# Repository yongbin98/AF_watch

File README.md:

# BAMI_watch

This repository contains the C code used in the PPG/ECG Wearable Devices for Atrial Fibrillation Diagnosis System thesis study. 

The code is designed for a smartwatch equipped with the following components:
- PPG sensor: MAX86171
- ECG sensor: MAX30003
- IMU sensor: LSM6DS
- LCD display: ST7789
- Battery monitoring chip: MAX17262
- Bluetooth module: E104-BT5005A
- Other components: SD card, switch, speaker

The following protocols are used:
- SD card: Fatfs
- ARM::CMSIS: ver 5.8.0
- ARM::DSP: ver 1.9.0

The hardware architectures:

The Developed wearable watch :

The code was developed in the Keil IDE.

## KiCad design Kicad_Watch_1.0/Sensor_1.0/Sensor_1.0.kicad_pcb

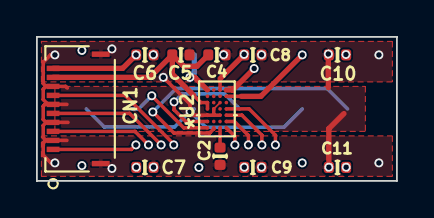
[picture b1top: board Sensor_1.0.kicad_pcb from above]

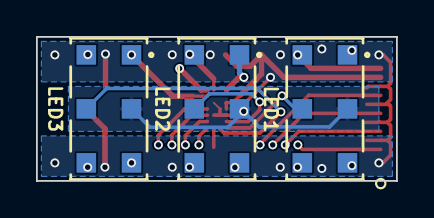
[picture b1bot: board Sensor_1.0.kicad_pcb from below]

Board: 4 copper layers, 20.0 x 8.0 mm, 14 parts (3 on the bottom side), 14 nets.

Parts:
C2: 1u; UL_C_0402_1005Metric
C4: 10u; UL_C_0402_1005Metric
C5: 0.1u; UL_C_0402_1005Metric
C6, C7, C8, C9, C10, C11: 22u; UL_C_0402_1005Metric
CN1: 503480-1000
LED1, LED2, LED3: SFH_7070; SFH7070
U2: MAX86171ENI+; MAX86171ENI&plus_

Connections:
+1V8: C4.1, C5.1, CN1.9, U2.D3 (VDD_ANA), U2.D4 (VDD_DIG)
/LED3_DRV: LED1.1, LED1.3, U2.A1 (LED3_DRV)
/LED4_DRV: LED2.1, LED2.3, U2.D1 (LED4_DRV)
/LED9_DRV: LED3.1, LED3.3, U2.A2 (LED9_DRV)
/PD1_IN: LED1.5, U2.D7 (PD1_IN)
/PD2_IN: LED2.5, U2.D6 (PD2_IN)
/PD3_IN: LED3.5, U2.C7 (PD3_IN)
/PPG_CS: CN1.7, U2.A7 (CSB/ADDR)
/PPG_MISO: CN1.3, U2.A5 (SDO)
/PPG_MOSI: CN1.5, U2.A6 (SDI/SDA)
/PPG_SCLK: CN1.1, U2.A4 (SCLK/SCL)
unnamed: C2.1, U2.B7 (VREF)
U_GND: C2.2, C4.2, C5.2, C6.2, C7.2, C8.2, C9.2, C10.2, C11.2, CN1.2, CN1.4, CN1.6, CN1.8, CN1.11, CN1.12, LED1.2, LED2.2, LED3.2, U2.B3 (PGND), U2.B5 (TRIG), U2.C4 (I2C_SEL), U2.C5 (GND), U2.D5 (PD_GND)
VDD: C6.1, C7.1, C8.1, C9.1, C10.1, C11.1, CN1.10, LED1.4, LED1.6, LED2.4, LED2.6, LED3.4, LED3.6, U2.B1 (VLED)

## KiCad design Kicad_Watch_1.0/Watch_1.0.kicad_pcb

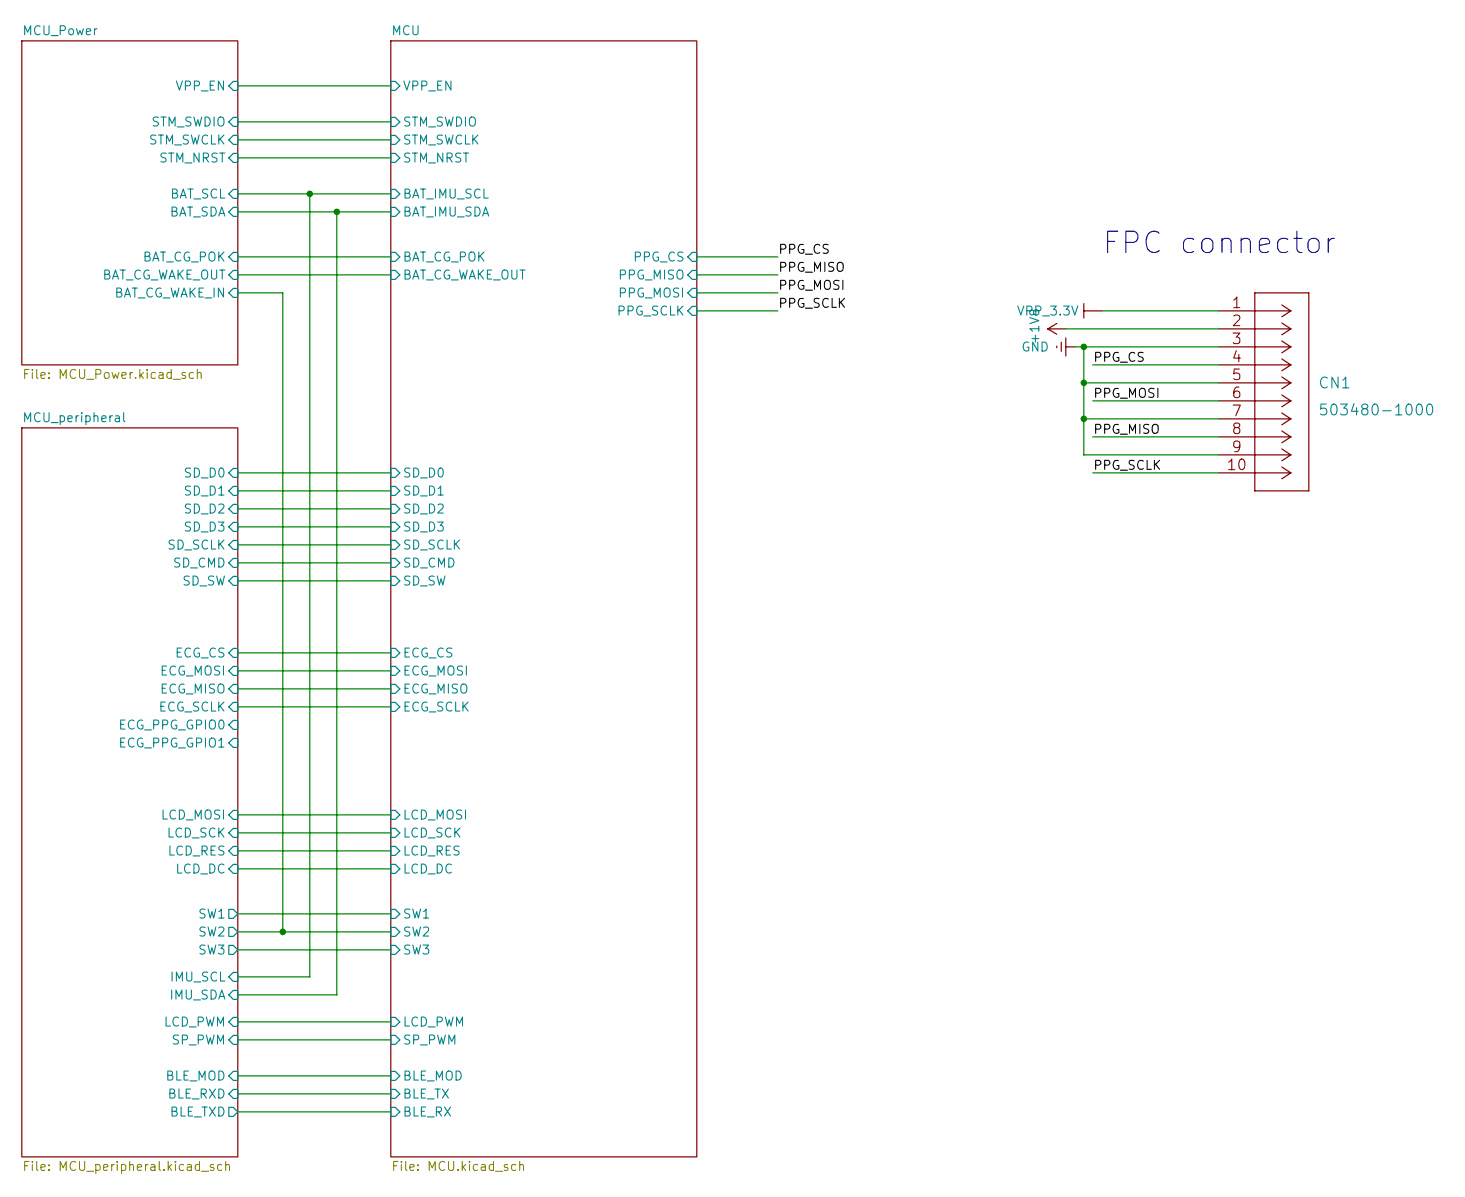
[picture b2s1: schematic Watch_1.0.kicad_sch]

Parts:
CN1: 503480-1000

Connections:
+1V8: CN1.2; also elsewhere on the board
/PPG_CS: CN1.4; also elsewhere on the board
/PPG_MISO: CN1.8; also elsewhere on the board
/PPG_MOSI: CN1.6; also elsewhere on the board
/PPG_SCLK: CN1.10; also elsewhere on the board
U_GND: CN1.3, CN1.5, CN1.7, CN1.9, CN1.11, CN1.12; also elsewhere on the board
VPP_3_3V: CN1.1; also elsewhere on the board

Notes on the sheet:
FPC connector

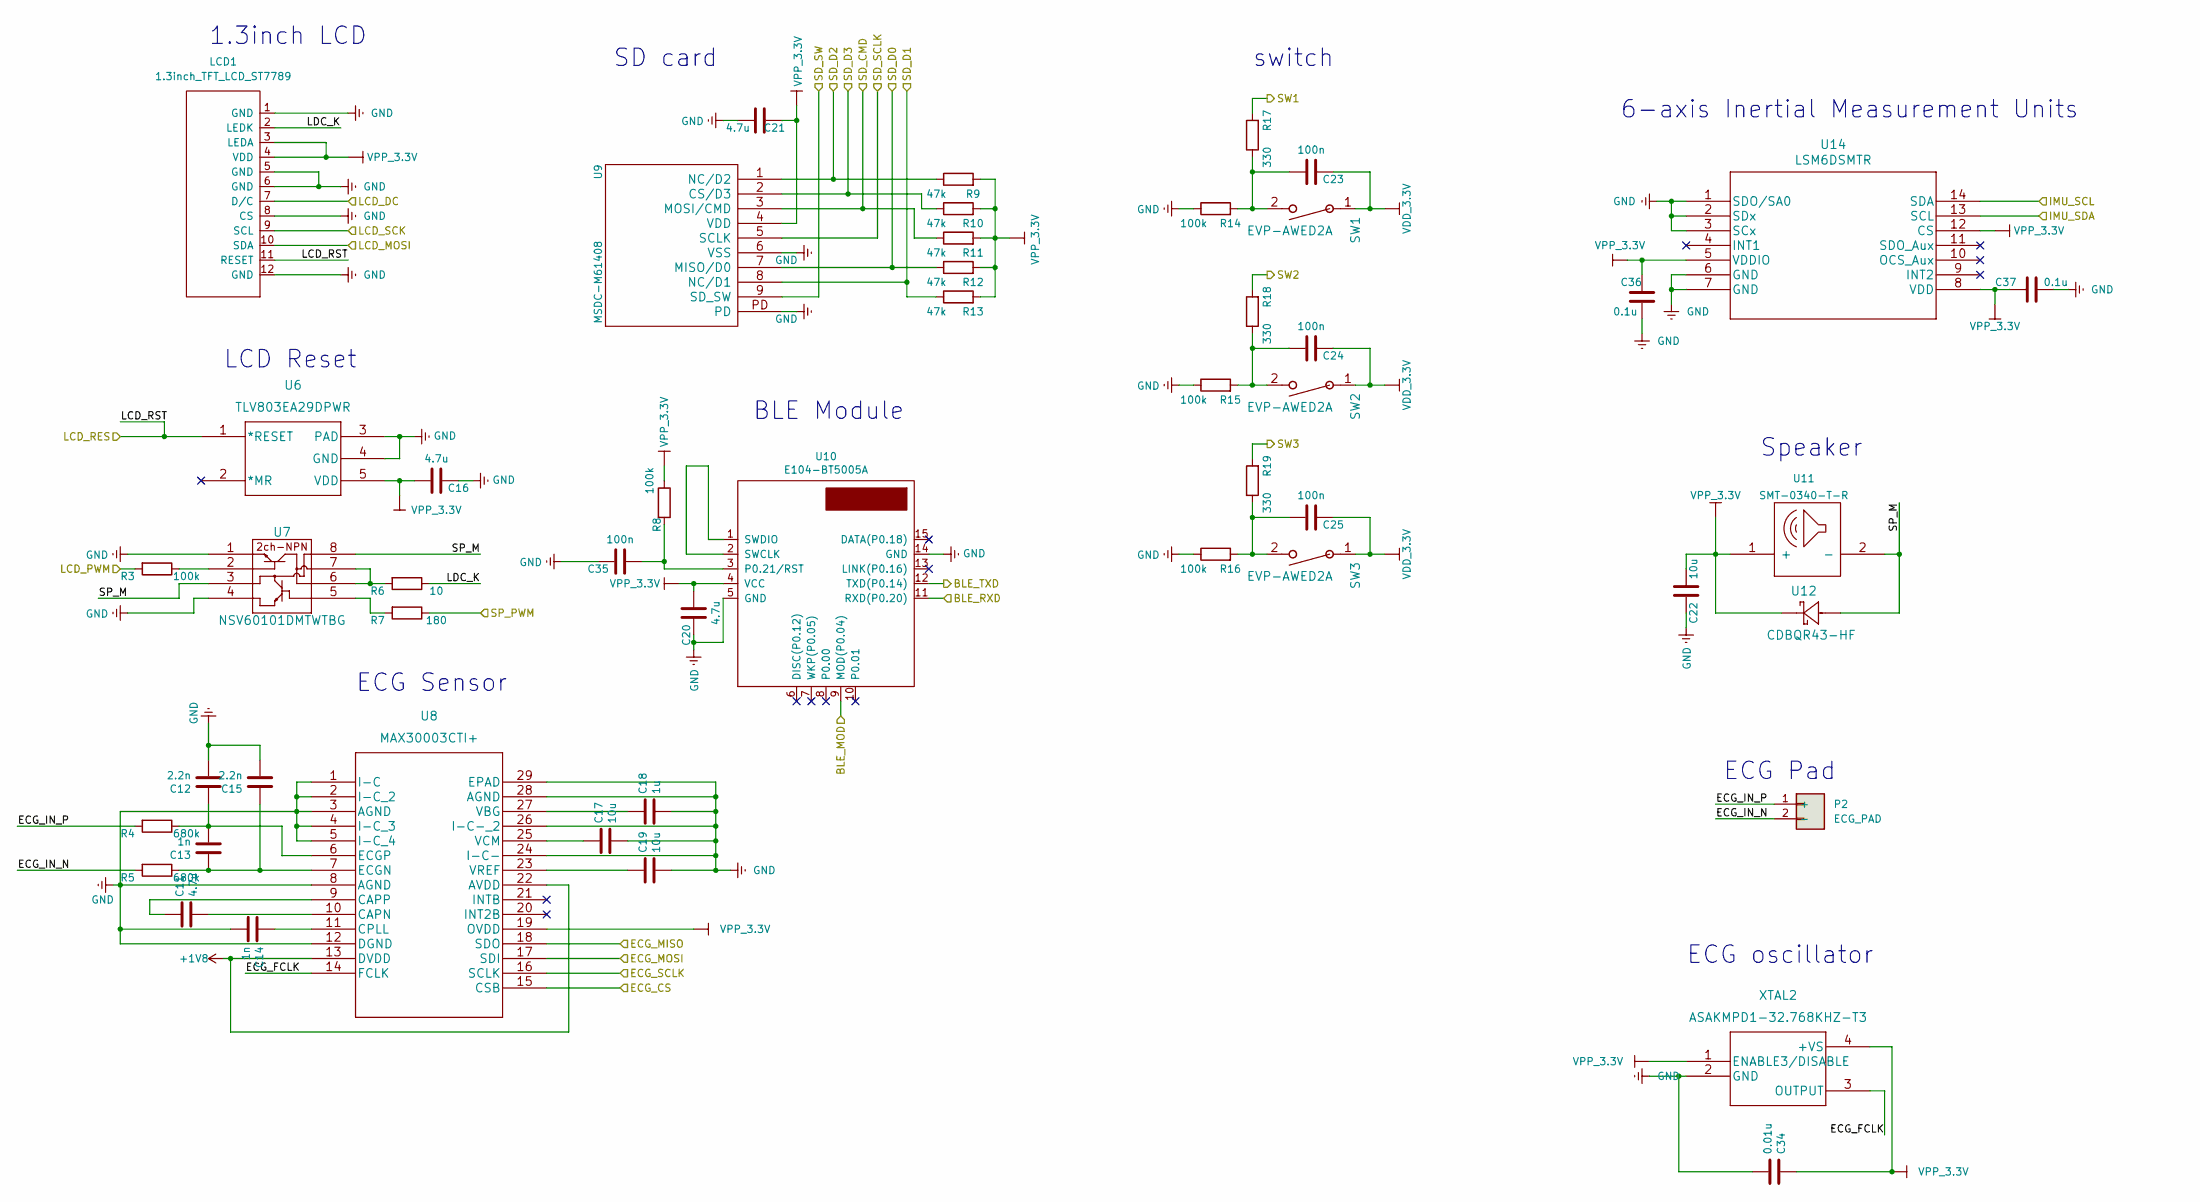
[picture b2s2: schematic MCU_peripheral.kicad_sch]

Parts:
C11, C16, C20, C21: 4.7u; UL_C_0402_1005Metric
C12, C15: 2.2n; UL_C_0402_1005Metric
C13, C14: 1n; UL_C_0402_1005Metric
C17, C19, C22: 10u; UL_C_0402_1005Metric
C18: 1u; UL_C_0402_1005Metric
C23, C24, C25, C35: 100n; UL_C_0402_1005Metric
C34: 0.01u; UL_C_0402_1005Metric
C36, C37: 0.1u; UL_C_0402_1005Metric
LCD1: 1.3inch_TFT_LCD_ST7789
P2: ECG_PAD
R3, R8, R14, R15, R16: 100k; R_0402_1005Metric
R4, R5: 680k; R_0402_1005Metric
R6: 10; R_0402_1005Metric
R7: 180; R_0402_1005Metric
R9, R10, R11, R12, R13: 47k; R_0402_1005Metric
R17, R18, R19: 330; R_0402_1005Metric
SW1, SW2, SW3: EVP-AWED2A
U6: TLV803EA29DPWR
U7: NSV60101DMTWTBG
U8: MAX30003CTI+; MAX30003CTI&plus_
U9: MSDC-M61408; MSDC-M61408(Micro_SD)
U10: E104-BT5005A; E104-BT5005A_QFN-15_9x9_Pitch1.1mm
U11: SMT-0340-T-R
U12: CDBQR43-HF
U14: LSM6DSMTR
XTAL2: ASAKMPD1-32.768KHZ-T3

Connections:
+1V8: U8.13 (DVDD), U8.22 (AVDD); also elsewhere on the board
/MCU/BAT_IMU_SCL: U14.14 (SDA); also elsewhere on the board
/MCU/BAT_IMU_SDA: U14.13 (SCL); also elsewhere on the board
/MCU/BLE_MOD: U10.9 (MOD(P0.04)); also elsewhere on the board
/MCU/BLE_RX: U10.12 (TXD(P0.14)); also elsewhere on the board
/MCU/BLE_TX: U10.11 (RXD(P0.20)); also elsewhere on the board
/MCU/ECG_CS: U8.15 (CSB); also elsewhere on the board
/MCU/ECG_MISO: U8.18 (SDO); also elsewhere on the board
/MCU/ECG_MOSI: U8.17 (SDI); also elsewhere on the board
/MCU/ECG_SCLK: U8.16 (SCLK); also elsewhere on the board
/MCU/LCD_DC: LCD1.7 (D/C); also elsewhere on the board
/MCU/LCD_MOSI: LCD1.10 (SDA); also elsewhere on the board
/MCU/LCD_PWM: R3.2; also elsewhere on the board
/MCU/LCD_SCK: LCD1.9 (SCL); also elsewhere on the board
/MCU/SD_CMD: R11.1, U9.3 (MOSI/CMD); also elsewhere on the board
/MCU/SD_D0: R12.1, U9.7 (MISO/D0); also elsewhere on the board
/MCU/SD_D1: R13.1, U9.8 (NC/D1); also elsewhere on the board
/MCU/SD_D2: R9.1, U9.1 (NC/D2); also elsewhere on the board
/MCU/SD_D3: R10.1, U9.2 (CS/D3); also elsewhere on the board
/MCU/SD_SCLK: U9.5 (SCLK); also elsewhere on the board
/MCU/SD_SW: U9.9 (SD_SW); also elsewhere on the board
/MCU/SP_PWM: R7.1; also elsewhere on the board
/MCU/SW1: R17.2; also elsewhere on the board
/MCU/SW2: R18.2; also elsewhere on the board
/MCU/SW3: R19.2; also elsewhere on the board
/MCU_peripheral/ECG_FCLK: U8.14 (FCLK), XTAL2.3 (OUTPUT)
/MCU_peripheral/ECG_IN_N: P2.2 (-), R5.2
/MCU_peripheral/ECG_IN_P: P2.1 (+), R4.2
/MCU_peripheral/LCD_RST: LCD1.11 (RESET), U6.1 (*RESET); also elsewhere on the board
/MCU_peripheral/LDC_K: LCD1.2 (LEDK), R6.1
/MCU_peripheral/SP_M: U7.3, U7.8, U11.2 (-), U12.2
unnamed: C11.1, U8.9 (CAPP)
unnamed: C11.2, U8.10 (CAPN)
unnamed: C12.1, C13.2, R4.1, U8.6 (ECGP)
unnamed: C13.1, C15.1, R5.1, U8.7 (ECGN)
unnamed: C14.1, U8.11 (CPLL)
unnamed: C17.1, U8.25 (VCM)
unnamed: C18.1, U8.27 (VBG)
unnamed: C19.1, U8.23 (VREF)
unnamed: C23.2, R14.2, R17.1, SW1.2
unnamed: C24.2, R15.2, R18.1, SW2.2
unnamed: C25.2, R16.2, R19.1, SW3.2
unnamed: C35.2, R8.2, U10.3 (P0.21/RST)
unnamed: R3.1, U7.2
unnamed: R6.2, U7.6, U7.7
unnamed: R7.2, U7.5
unnamed: U10.1 (SWDIO), U10.2 (SWCLK)
U_GND: C12.2, C14.2, C15.2, C16.1, C17.2, C18.2, C19.2, C20.1, C21.1, C22.1, C34.2, C35.1, C36.2, C37.2, LCD1.1 (GND), LCD1.5 (GND), LCD1.6 (GND), LCD1.8 (CS), LCD1.12 (GND), R14.1, R15.1, R16.1, U6.3 (PAD), U6.4 (GND), U7.1, U7.4, U8.1 (I-C), U8.2 (I-C_2), U8.3 (AGND), U8.4 (I-C_3), U8.5 (I-C_4), U8.8 (AGND), U8.12 (DGND), U8.24 (I-C-), U8.26 (I-C-_2), U8.28 (AGND), U8.29 (EPAD), U9.6 (VSS), U9.PD, U10.5 (GND), U10.14 (GND), U14.1 (SDO/SA0), U14.2 (SDx), U14.3 (SCx), U14.6 (GND), U14.7 (GND), XTAL2.2 (GND); also elsewhere on the board
VDD_3_3V: C23.1, C24.1, C25.1, SW1.1, SW2.1, SW3.1; also elsewhere on the board
VPP_3_3V: C16.2, C20.2, C21.2, C22.2, C34.1, C36.1, C37.1, LCD1.3 (LEDA), LCD1.4 (VDD), R8.1, R9.2, R10.2, R11.2, R12.2, R13.2, U6.5 (VDD), U8.19 (OVDD), U9.4 (VDD), U10.4 (VCC), U11.1 (+), U12.1, U14.5 (VDDIO), U14.8 (VDD), U14.12 (CS), XTAL2.1 (ENABLE3/DISABLE), XTAL2.4 (+VS); also elsewhere on the board

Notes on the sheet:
6-axis Inertial Measurement Units
Speaker
switch
ECG Pad
1.3inch LCD
LCD Reset
BLE Module
SD card
ECG oscillator
ECG Sensor

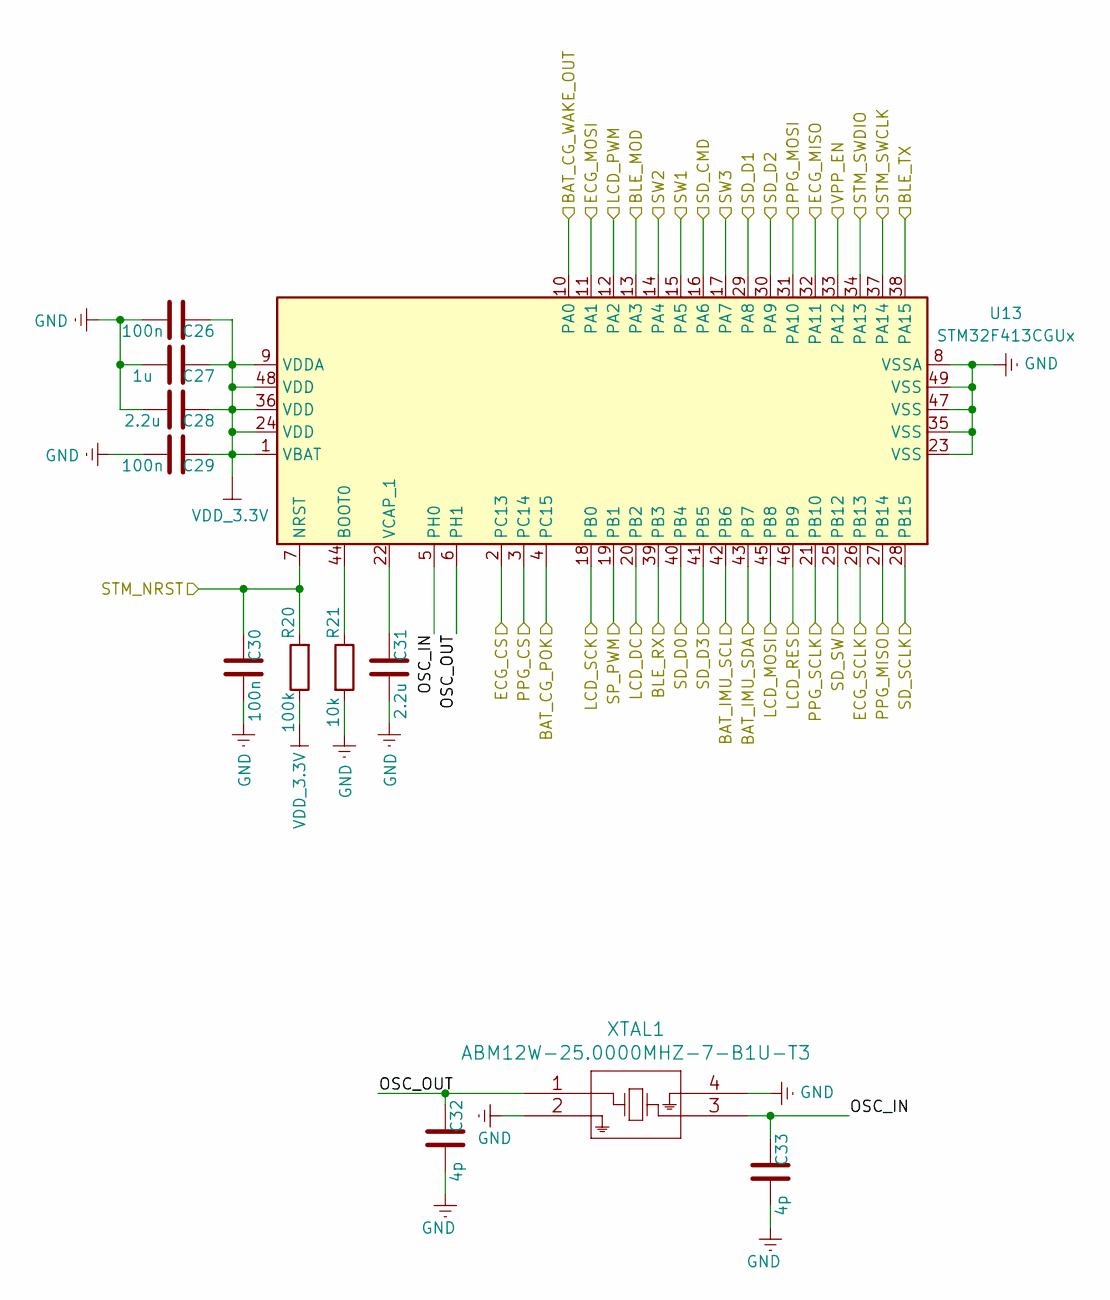
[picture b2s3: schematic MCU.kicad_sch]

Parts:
C26, C29, C30: 100n; UL_C_0402_1005Metric
C27: 1u; UL_C_0402_1005Metric
C28, C31: 2.2u; UL_C_0402_1005Metric
C32, C33: 4p; UL_C_0402_1005Metric
R20: 100k; R_0402_1005Metric
R21: 10k; R_0402_1005Metric
U13: STM32F413CGUx; QFN-48-1EP_7x7mm_P0.5mm_EP5.6x5.6mm
XTAL1: ABM12W-25.0000MHZ-7-B1U-T3; ABM12W

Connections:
/MCU/BAT_CG_POK: U13.4 (PC15); also elsewhere on the board
/MCU/BAT_CG_WAKE_OUT: U13.10 (PA0); also elsewhere on the board
/MCU/BAT_IMU_SCL: U13.42 (PB6); also elsewhere on the board
/MCU/BAT_IMU_SDA: U13.43 (PB7); also elsewhere on the board
/MCU/BLE_MOD: U13.13 (PA3); also elsewhere on the board
/MCU/BLE_RX: U13.39 (PB3); also elsewhere on the board
/MCU/BLE_TX: U13.38 (PA15); also elsewhere on the board
/MCU/ECG_CS: U13.2 (PC13); also elsewhere on the board
/MCU/ECG_MISO: U13.32 (PA11); also elsewhere on the board
/MCU/ECG_MOSI: U13.11 (PA1); also elsewhere on the board
/MCU/ECG_SCLK: U13.26 (PB13); also elsewhere on the board
/MCU/LCD_DC: U13.20 (PB2); also elsewhere on the board
/MCU/LCD_MOSI: U13.45 (PB8); also elsewhere on the board
/MCU/LCD_PWM: U13.12 (PA2); also elsewhere on the board
/MCU/LCD_SCK: U13.18 (PB0); also elsewhere on the board
/MCU/OSC_IN: C33.2, U13.5 (PH0), XTAL1.3
/MCU/OSC_OUT: C32.2, U13.6 (PH1), XTAL1.1
/MCU/SD_CMD: U13.16 (PA6); also elsewhere on the board
/MCU/SD_D0: U13.40 (PB4); also elsewhere on the board
/MCU/SD_D1: U13.29 (PA8); also elsewhere on the board
/MCU/SD_D2: U13.30 (PA9); also elsewhere on the board
/MCU/SD_D3: U13.41 (PB5); also elsewhere on the board
/MCU/SD_SCLK: U13.28 (PB15); also elsewhere on the board
/MCU/SD_SW: U13.25 (PB12); also elsewhere on the board
/MCU/SP_PWM: U13.19 (PB1); also elsewhere on the board
/MCU/STM_NRST: C30.2, R20.2, U13.7 (NRST); also elsewhere on the board
/MCU/STM_SWCLK: U13.37 (PA14); also elsewhere on the board
/MCU/STM_SWDIO: U13.34 (PA13); also elsewhere on the board
/MCU/SW1: U13.15 (PA5); also elsewhere on the board
/MCU/SW2: U13.14 (PA4); also elsewhere on the board
/MCU/SW3: U13.17 (PA7); also elsewhere on the board
/MCU/VPP_EN: U13.33 (PA12); also elsewhere on the board
/MCU_peripheral/LCD_RST: U13.46 (PB9); also elsewhere on the board
/PPG_CS: U13.3 (PC14); also elsewhere on the board
/PPG_MISO: U13.27 (PB14); also elsewhere on the board
/PPG_MOSI: U13.31 (PA10); also elsewhere on the board
/PPG_SCLK: U13.21 (PB10); also elsewhere on the board
unnamed: C31.2, U13.22 (VCAP_1)
unnamed: R21.1, U13.44 (BOOT0)
U_GND: C26.1, C27.1, C28.1, C29.1, C30.1, C31.1, C32.1, C33.1, R21.2, U13.8 (VSSA), U13.23 (VSS), U13.35 (VSS), U13.47 (VSS), U13.49 (VSS), XTAL1.2, XTAL1.4; also elsewhere on the board
VDD_3_3V: C26.2, C27.2, C28.2, C29.2, R20.1, U13.1 (VBAT), U13.9 (VDDA), U13.24 (VDD), U13.36 (VDD), U13.48 (VDD); also elsewhere on the board

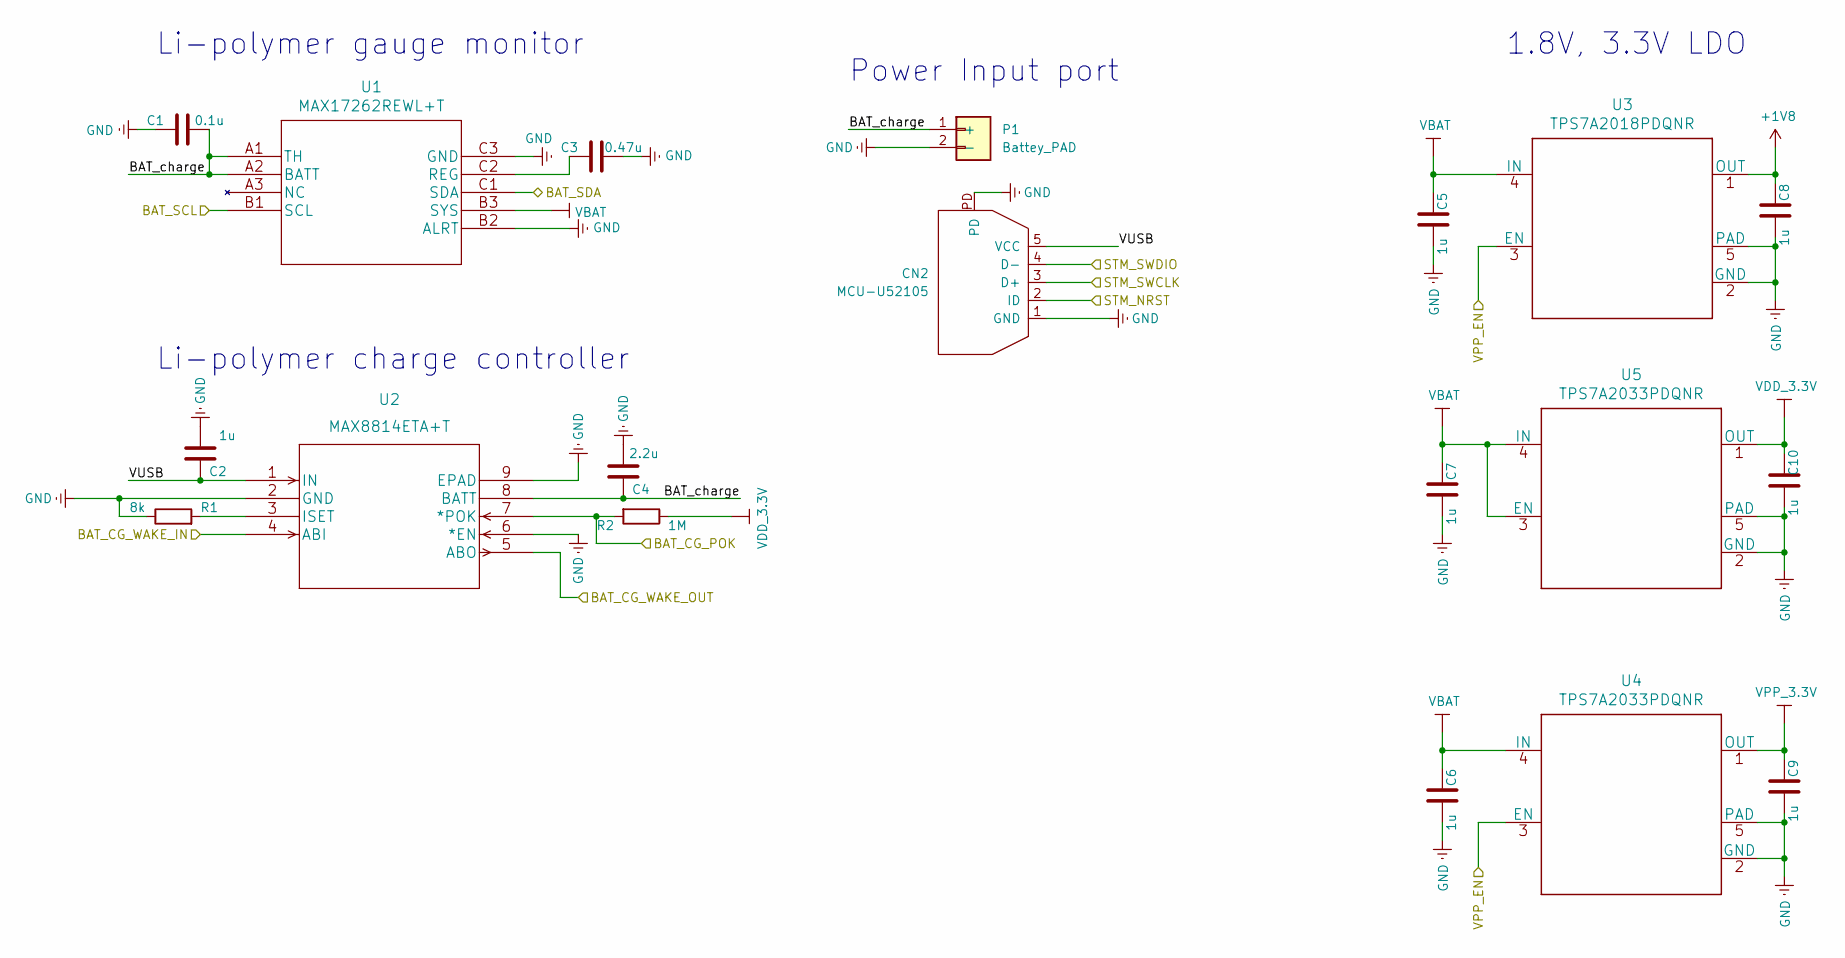
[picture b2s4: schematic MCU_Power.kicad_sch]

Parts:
C1: 0.1u; UL_C_0402_1005Metric
C2, C5, C6, C7, C8, C9, C10: 1u; UL_C_0402_1005Metric
C3: 0.47u; UL_C_0402_1005Metric
C4: 2.2u; UL_C_0402_1005Metric
CN2: MCU-U52105
P1: Battey_PAD
R1: 8k; R_0402_1005Metric
R2: 1M; R_0402_1005Metric
U1: MAX17262REWL+T; MAX17262REWL&plus_T
U2: MAX8814ETA+T; MAX8814ETA&plus_T
U3: TPS7A2018PDQNR; X2SON-4PIN
U4, U5: TPS7A2033PDQNR; X2SON-4PIN

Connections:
+1V8: C8.2, U3.1 (OUT); also elsewhere on the board
/MCU/BAT_CG_POK: R2.2, U2.7 (*POK); also elsewhere on the board
/MCU/BAT_CG_WAKE_OUT: U2.5 (ABO); also elsewhere on the board
/MCU/BAT_IMU_SCL: U1.B1 (SCL); also elsewhere on the board
/MCU/BAT_IMU_SDA: U1.C1 (SDA); also elsewhere on the board
/MCU/STM_NRST: CN2.2 (ID); also elsewhere on the board
/MCU/STM_SWCLK: CN2.3 (D+); also elsewhere on the board
/MCU/STM_SWDIO: CN2.4 (D-); also elsewhere on the board
/MCU/SW2: U2.4 (ABI); also elsewhere on the board
/MCU/VPP_EN: U3.3 (EN), U4.3 (EN); also elsewhere on the board
/MCU_Power/BAT_charge: C1.2, C4.1, P1.1 (+), U1.A1 (TH), U1.A2 (BATT), U2.8 (BATT)
/MCU_Power/VUSB: C2.1, CN2.5 (VCC), U2.1 (IN)
unnamed: C3.2, U1.C2 (REG)
unnamed: R1.2, U2.3 (ISET)
U_GND: C1.1, C2.2, C3.1, C4.2, C5.1, C6.1, C7.1, C8.1, C9.1, C10.1, CN2.1 (GND), CN2.PD, P1.2 (-), R1.1, U1.B2 (ALRT), U1.C3 (GND), U2.2 (GND), U2.6 (*EN), U2.9 (EPAD), U3.2 (GND), U3.5 (PAD), U4.2 (GND), U4.5 (PAD), U5.2 (GND), U5.5 (PAD); also elsewhere on the board
VBAT: C5.2, C6.2, C7.2, U1.B3 (SYS), U3.4 (IN), U4.4 (IN), U5.3 (EN), U5.4 (IN)
VDD_3_3V: C10.2, R2.1, U5.1 (OUT); also elsewhere on the board
VPP_3_3V: C9.2, U4.1 (OUT); also elsewhere on the board

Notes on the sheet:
Li-polymer charge controller
Li-polymer gauge monitor
1.8V, 3.3V LDO
Power Input port

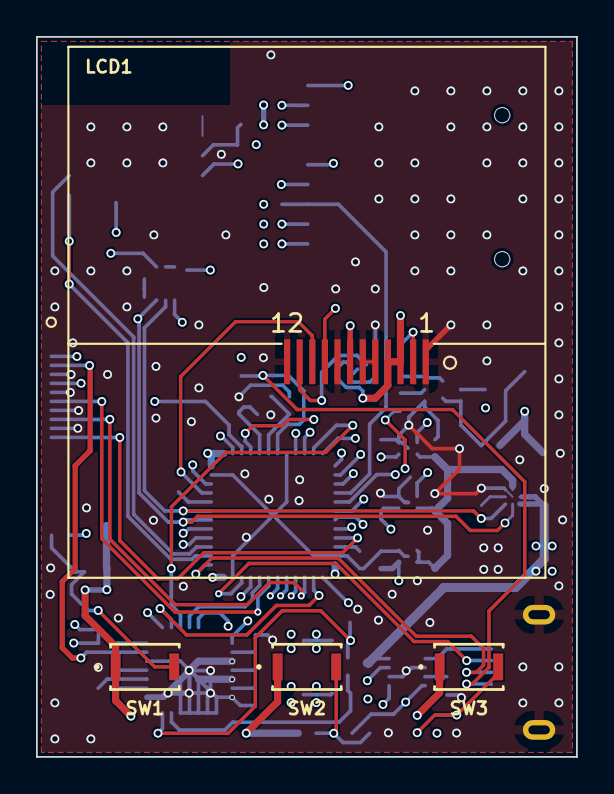
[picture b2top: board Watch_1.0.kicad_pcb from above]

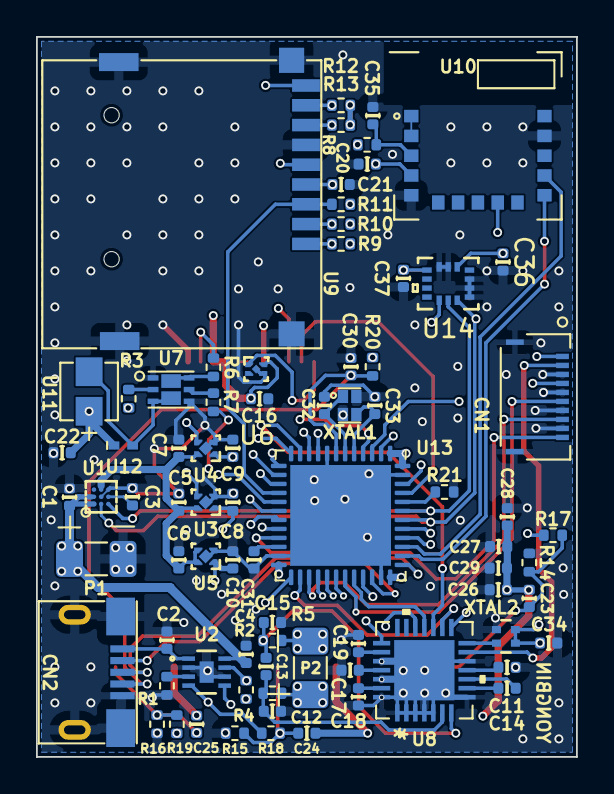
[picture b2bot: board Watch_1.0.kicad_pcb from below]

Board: 4 copper layers, 30.0 x 40.0 mm, 82 parts (78 on the bottom side), 69 nets.

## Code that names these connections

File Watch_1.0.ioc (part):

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Mcu.Name=STM32F413C(G-H)Ux
Mcu.Package=UFQFPN48
Mcu.UserName=STM32F413CGUx
PA0.GPIOParameters=GPIO_Label
PA0.GPIO_Label=BAT_CG_WAKE_OUT
PA0.Mode=SYS_WakeUp0
PA0.Signal=SYS_WKUP1
PA1.GPIOParameters=GPIO_Label
PA1.GPIO_Label=ECG_MOSI
PA1.Mode=Full_Duplex_Master
PA1.Signal=SPI4_MOSI
PA10.GPIOParameters=GPIO_Label
PA10.GPIO_Label=PPG_MOSI
PA10.Mode=Full_Duplex_Master
PA10.Signal=SPI2_MOSI
PA11.GPIOParameters=GPIO_Label
PA11.GPIO_Label=ECG_MISO
PA11.Mode=Full_Duplex_Master
PA11.Signal=SPI4_MISO
PA12.GPIOParameters=GPIO_Label
PA12.GPIO_Label=VPP_EN
PA12.Signal=GPIO_Output
PA13.Mode=Serial_Wire
PA13.Signal=SYS_JTMS-SWDIO
PA14.Mode=Serial_Wire
PA14.Signal=SYS_JTCK-SWCLK
PA15.GPIOParameters=GPIO_PuPd,GPIO_Label
PA15.GPIO_Label=BLE_TX
PA15.GPIO_PuPd=GPIO_NOPULL
PA15.Mode=Asynchronous
PA15.Signal=UART7_TX
PA2.GPIOParameters=GPIO_Label
PA2.GPIO_Label=LCD_PWM
PA2.Signal=S_TIM9_CH1
PA3.GPIOParameters=GPIO_Label
PA3.GPIO_Label=BLE_MOD
PA3.Signal=GPIO_Output
PA4.GPIOParameters=GPIO_Label
PA4.GPIO_Label=SW2
PA4.Signal=GPXTI4
PA5.GPIOParameters=GPIO_Label
PA5.GPIO_Label=SW1
PA5.Signal=GPXTI5
PA6.GPIOParameters=GPIO_Label
PA6.GPIO_Label=SD_CMD
PA6.Mode=SD_4_bits_Wide_bus
PA6.Signal=SDIO_CMD
PA7.GPIOParameters=GPIO_Label
PA7.GPIO_Label=SW3
PA7.Signal=GPXTI7
PA8.GPIOParameters=GPIO_Label
PA8.GPIO_Label=SD_D1
PA8.Mode=SD_4_bits_Wide_bus
PA8.Signal=SDIO_D1
PA9.GPIOParameters=GPIO_Label
PA9.GPIO_Label=SD_D2
PA9.Mode=SD_4_bits_Wide_bus
PA9.Signal=SDIO_D2
PB0.GPIOParameters=GPIO_PuPd,GPIO_Label
PB0.GPIO_Label=LCD_SCK
PB0.GPIO_PuPd=GPIO_PULLUP
PB0.Mode=Simplex_Bidirectional_Master
PB0.Signal=SPI5_SCK
PB1.GPIOParameters=GPIO_Label
PB1.GPIO_Label=SP_PWM
PB1.Signal=S_TIM3_CH4
PB10.GPIOParameters=GPIO_Label
PB10.GPIO_Label=PPG_SCK
PB10.Mode=Full_Duplex_Master
PB10.Signal=SPI2_SCK
PB12.GPIOParameters=GPIO_PuPd,GPIO_Label
PB12.GPIO_Label=SD_SW
PB12.GPIO_PuPd=GPIO_PULLUP
PB12.Signal=GPIO_Input
PB13.GPIOParameters=GPIO_Label
PB13.GPIO_Label=ECG_SCK
PB13.Mode=Full_Duplex_Master
PB13.Signal=SPI4_SCK
PB14.GPIOParameters=GPIO_Label
PB14.GPIO_Label=PPG_MISO
PB14.Mode=Full_Duplex_Master
PB14.Signal=SPI2_MISO
PB15.GPIOParameters=GPIO_Label
PB15.GPIO_Label=SD_CLK
PB15.Mode=SD_4_bits_Wide_bus
PB15.Signal=SDIO_CK
PB2.GPIOParameters=GPIO_Label
PB2.GPIO_Label=LCD_DC
PB2.Signal=GPIO_Output
PB3.GPIOParameters=GPIO_PuPd,GPIO_Label
PB3.GPIO_Label=BLE_RX
PB3.GPIO_PuPd=GPIO_NOPULL
PB3.Mode=Asynchronous
PB3.Signal=UART7_RX
PB4.GPIOParameters=GPIO_Label
PB4.GPIO_Label=SD_D0
PB4.Mode=SD_4_bits_Wide_bus
PB4.Signal=SDIO_D0
PB5.GPIOParameters=GPIO_Label
PB5.GPIO_Label=SD_D3
PB5.Mode=SD_4_bits_Wide_bus
PB5.Signal=SDIO_D3
PB6.GPIOParameters=GPIO_Label,GPIO_Pu
PB6.GPIO_Label=BAT_IMU_SCL
PB6.GPIO_Pu=GPIO_PULLUP
PB6.Mode=I2C
PB6.Signal=I2C1_SCL
PB7.GPIOParameters=GPIO_Label,GPIO_Pu
PB7.GPIO_Label=BAT_IMU_SDA
PB7.GPIO_Pu=GPIO_PULLUP
PB7.Mode=I2C
PB7.Signal=I2C1_SDA
PB8.GPIOParameters=GPIO_PuPd,GPIO_Label
PB8.GPIO_Label=LCD_MOSI
PB8.GPIO_PuPd=GPIO_PULLUP
PB8.Mode=Simplex_Bidirectional_Master
PB8.Signal=SPI5_MOSI
PB9.GPIOParameters=GPIO_Label
PB9.GPIO_Label=LCD_RES
PB9.Signal=GPIO_Output
PC13.GPIOParameters=GPIO_Label
PC13.GPIO_Label=ECG_CS
PC13.Signal=GPIO_Output
PC14-OSC32_IN.GPIOParameters=GPIO_Label
PC14-OSC32_IN.GPIO_Label=PPG_CS
PC14-OSC32_IN.Signal=GPIO_Output
PC15-OSC32_OUT.GPIOParameters=GPIO_PuPd,GPIO_Label
PC15-OSC32_OUT.GPIO_Label=BAT_CG_POK
PC15-OSC32_OUT.GPIO_PuPd=GPIO_PULLUP
PC15-OSC32_OUT.Signal=GPIO_Input
PH0\ -\ OSC_IN.Mode=HSE-External-Oscillator
PH0\ -\ OSC_IN.Signal=RCC_OSC_IN
PH1\ -\ OSC_OUT.Mode=HSE-External-Oscillator
PH1\ -\ OSC_OUT.Signal=RCC_OSC_OUT
RCC.SYSCLKFreq_VALUE=50000000
RCC.SYSCLKSource=RCC_SYSCLKSOURCE_PLLCLK
board=custom

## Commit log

2022-11-17 AF detect
2023-04-04 selective Afib detection prototype

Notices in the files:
parts and their libraries:
Copyright 2021 Accelerated Designs. All rights reserved.
